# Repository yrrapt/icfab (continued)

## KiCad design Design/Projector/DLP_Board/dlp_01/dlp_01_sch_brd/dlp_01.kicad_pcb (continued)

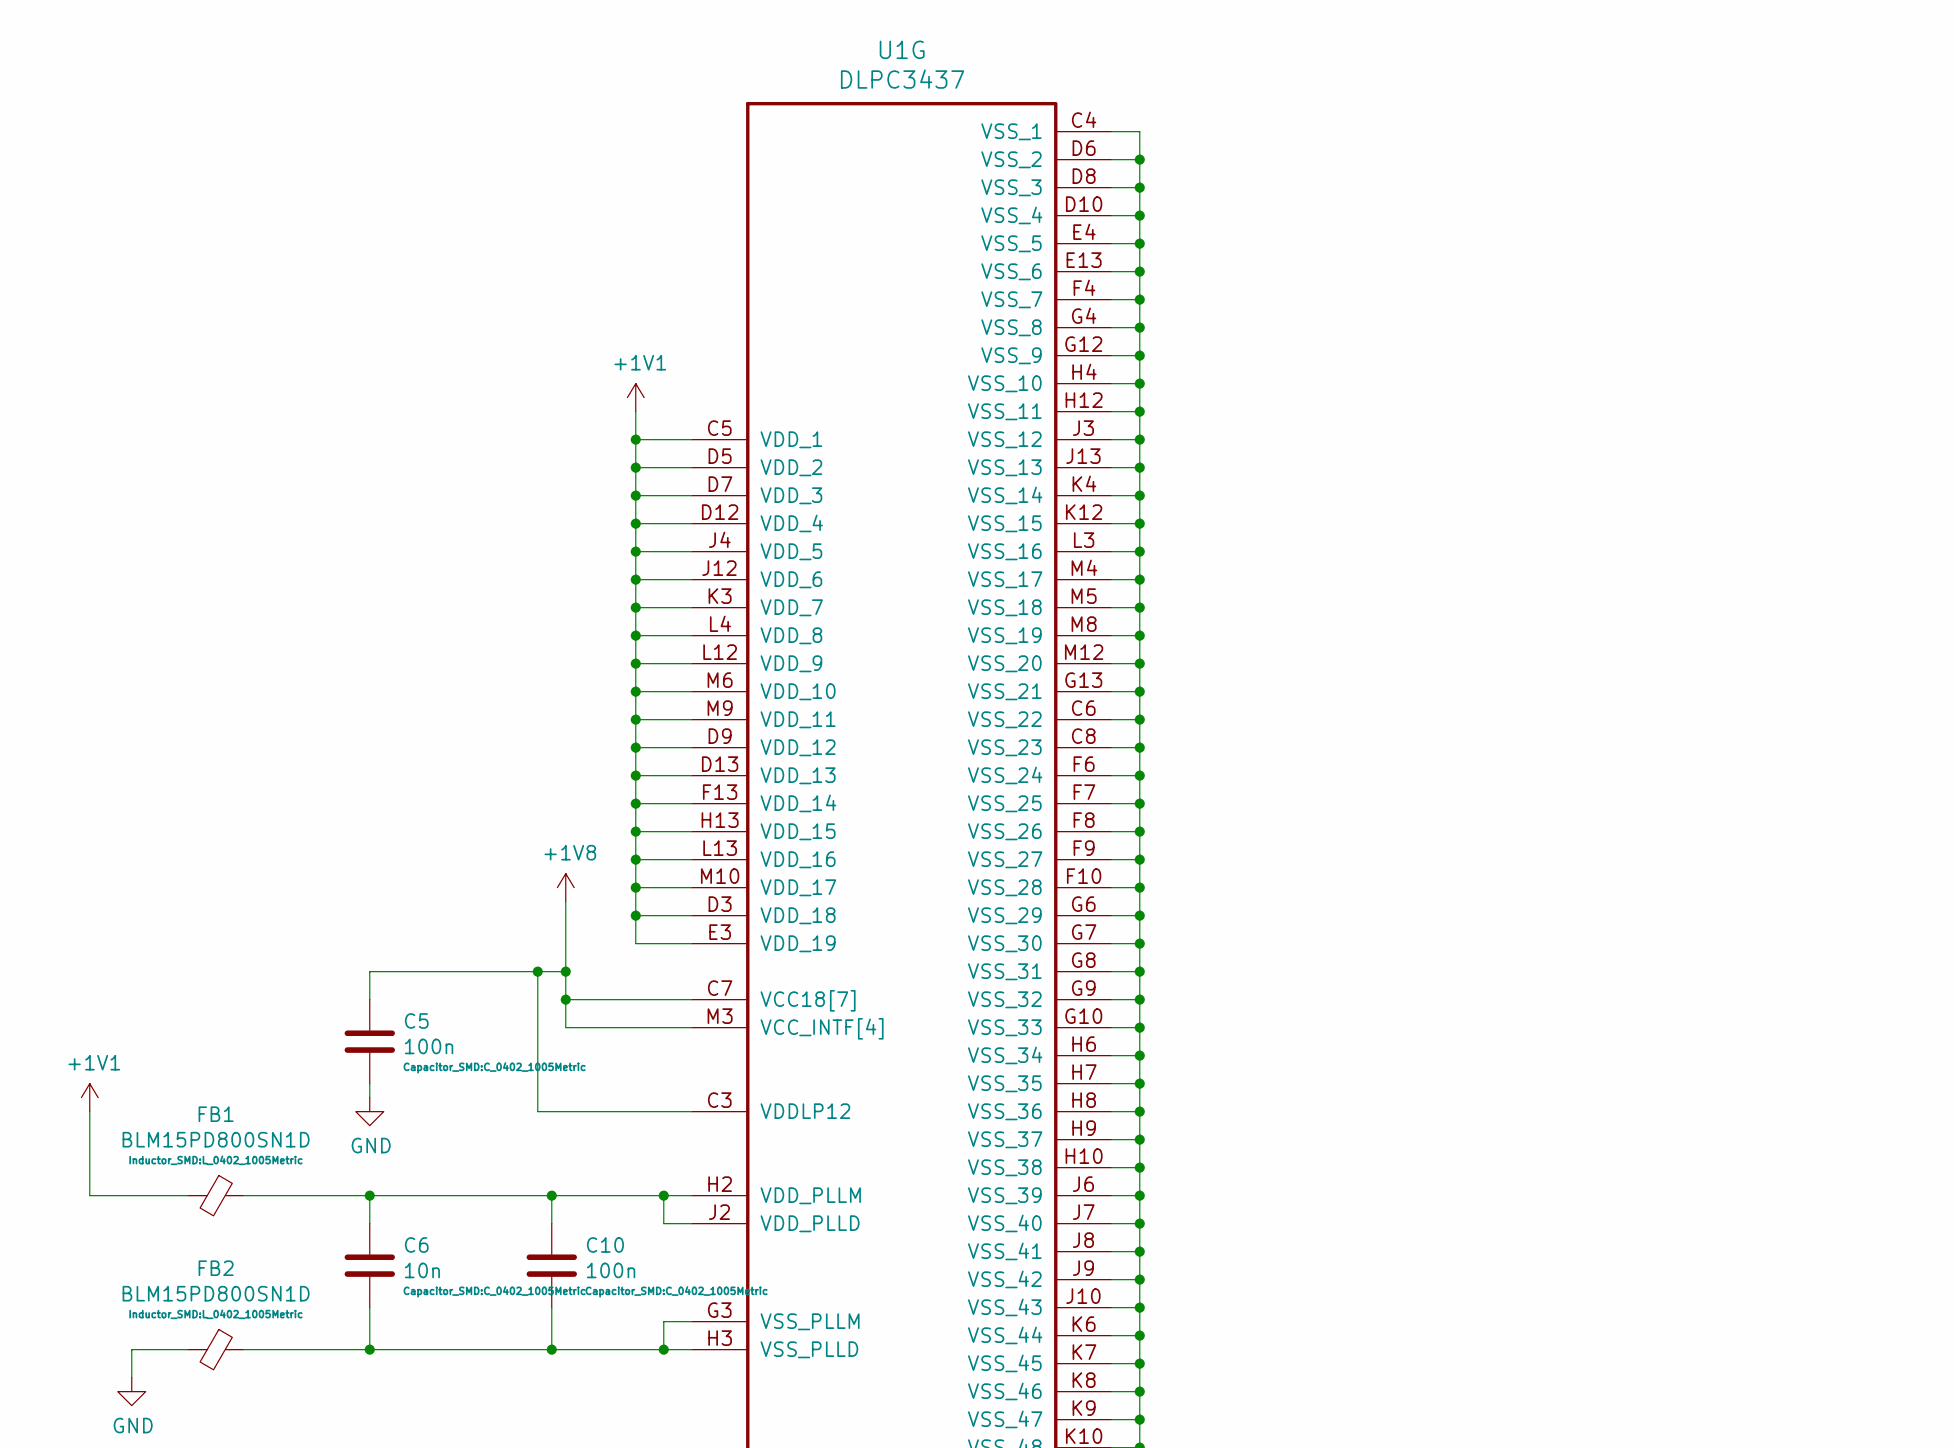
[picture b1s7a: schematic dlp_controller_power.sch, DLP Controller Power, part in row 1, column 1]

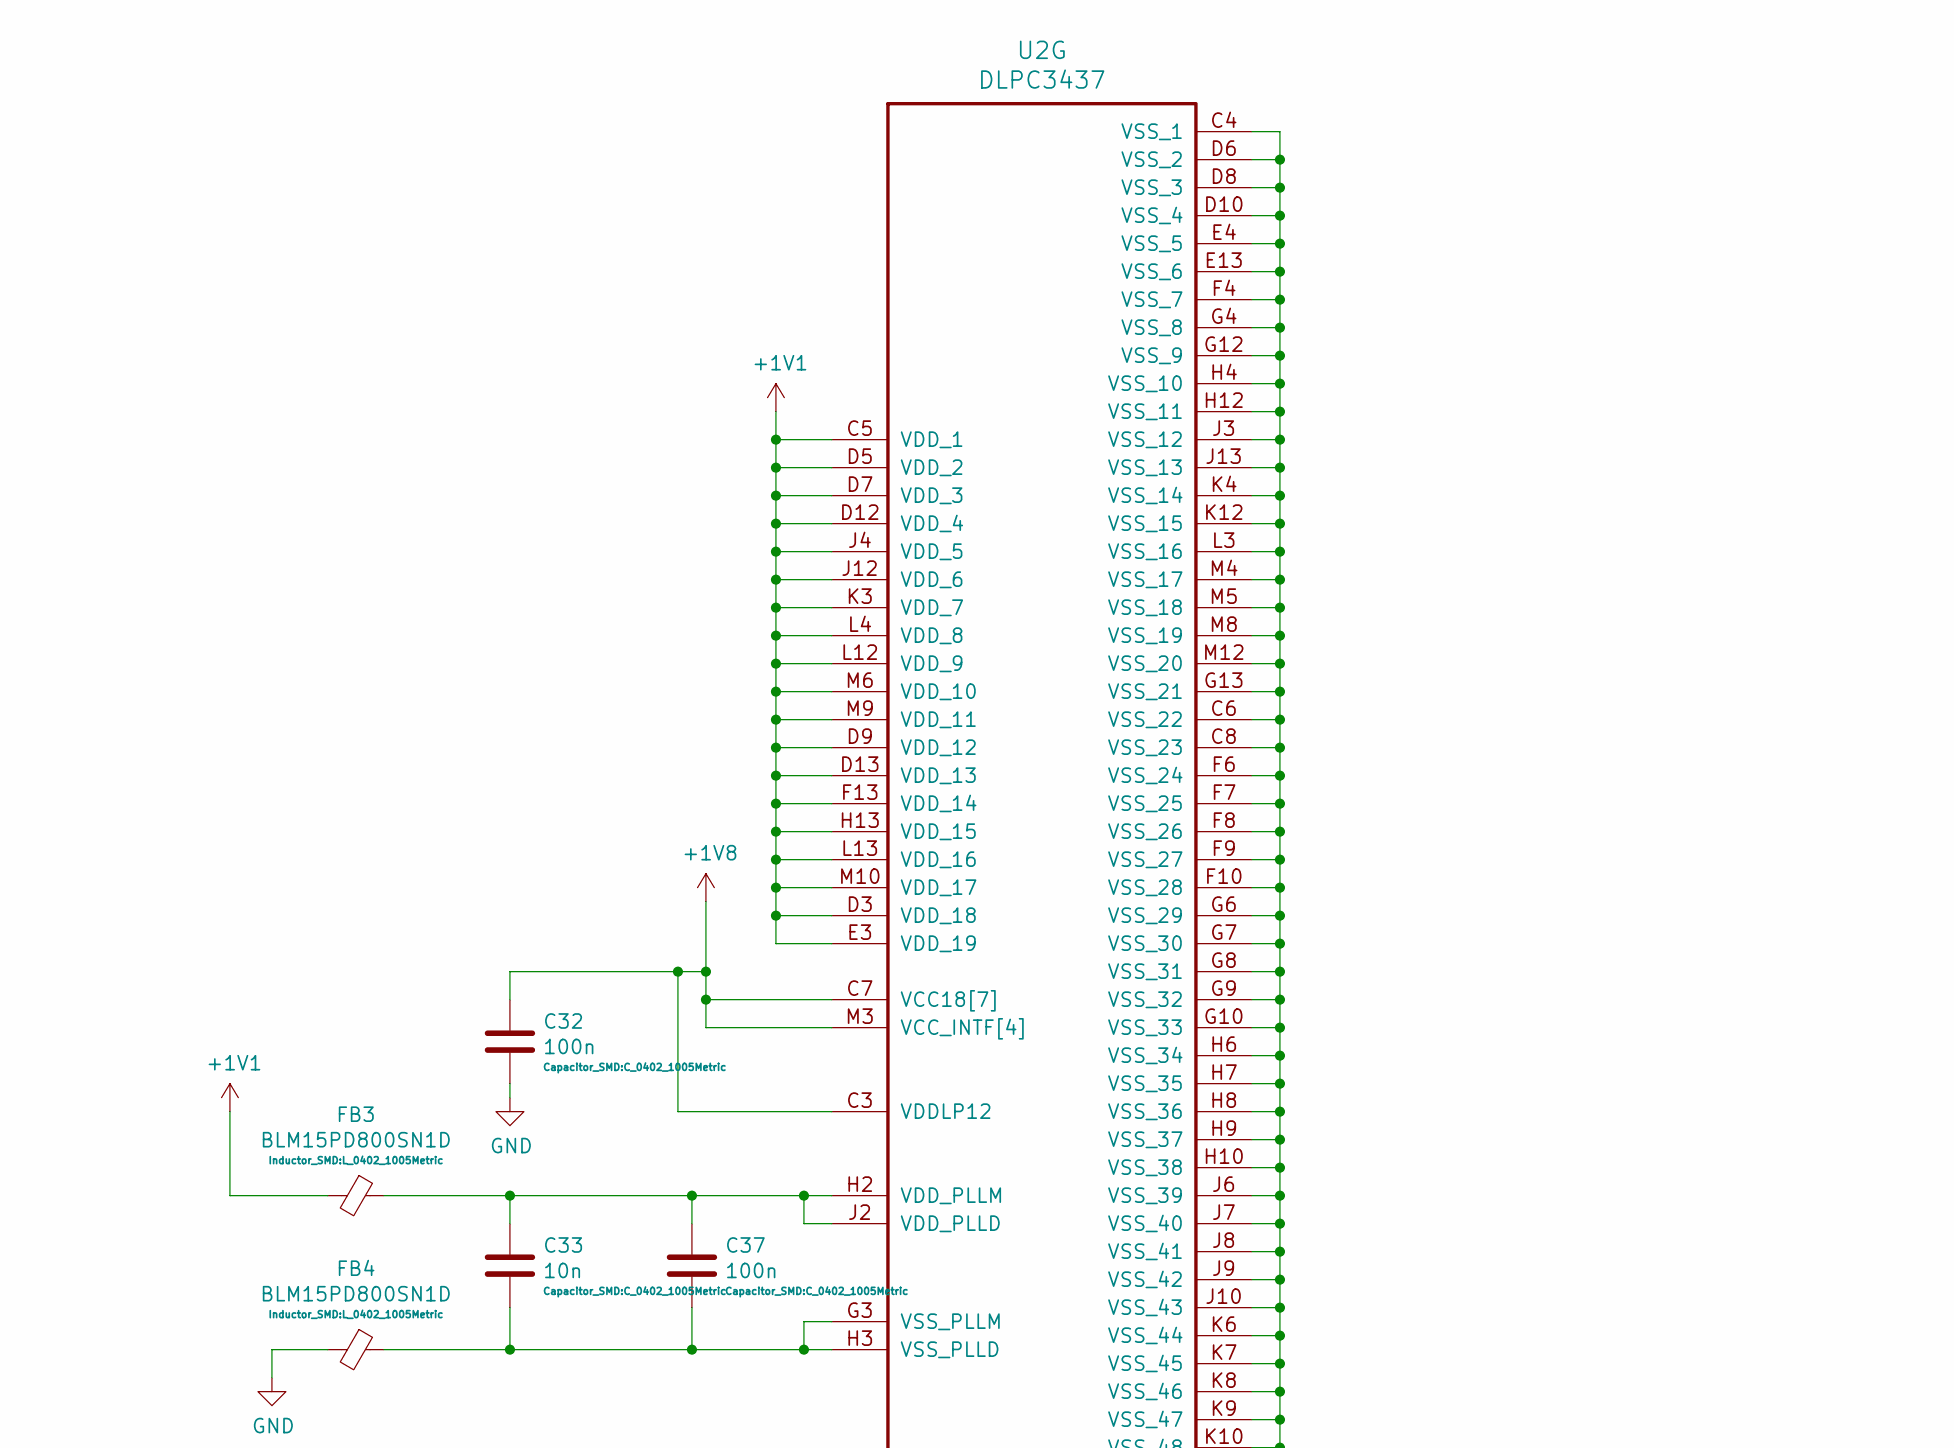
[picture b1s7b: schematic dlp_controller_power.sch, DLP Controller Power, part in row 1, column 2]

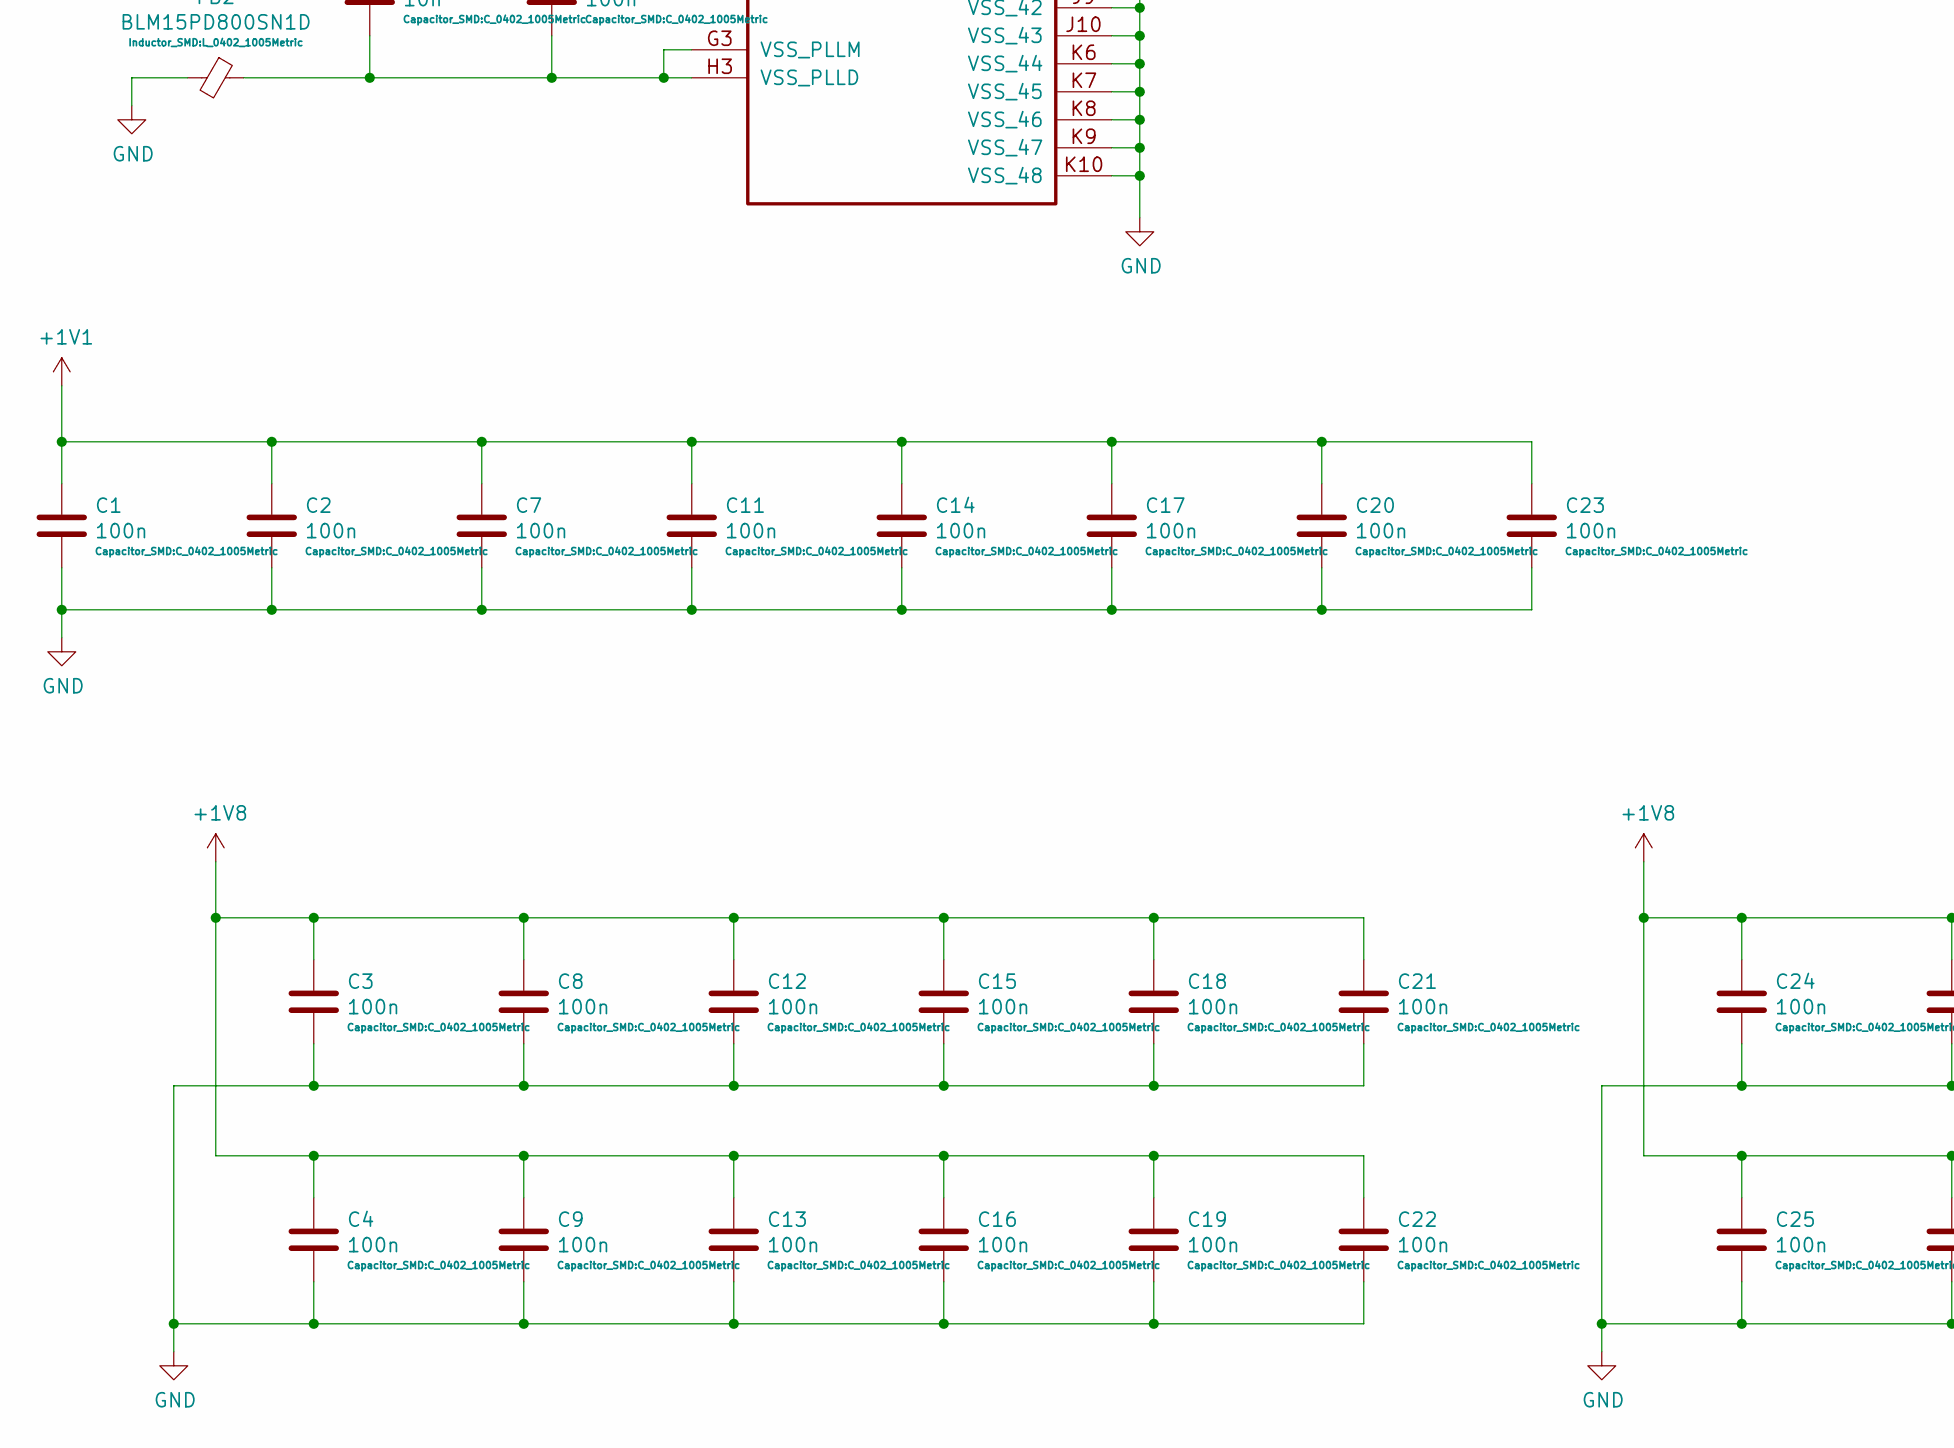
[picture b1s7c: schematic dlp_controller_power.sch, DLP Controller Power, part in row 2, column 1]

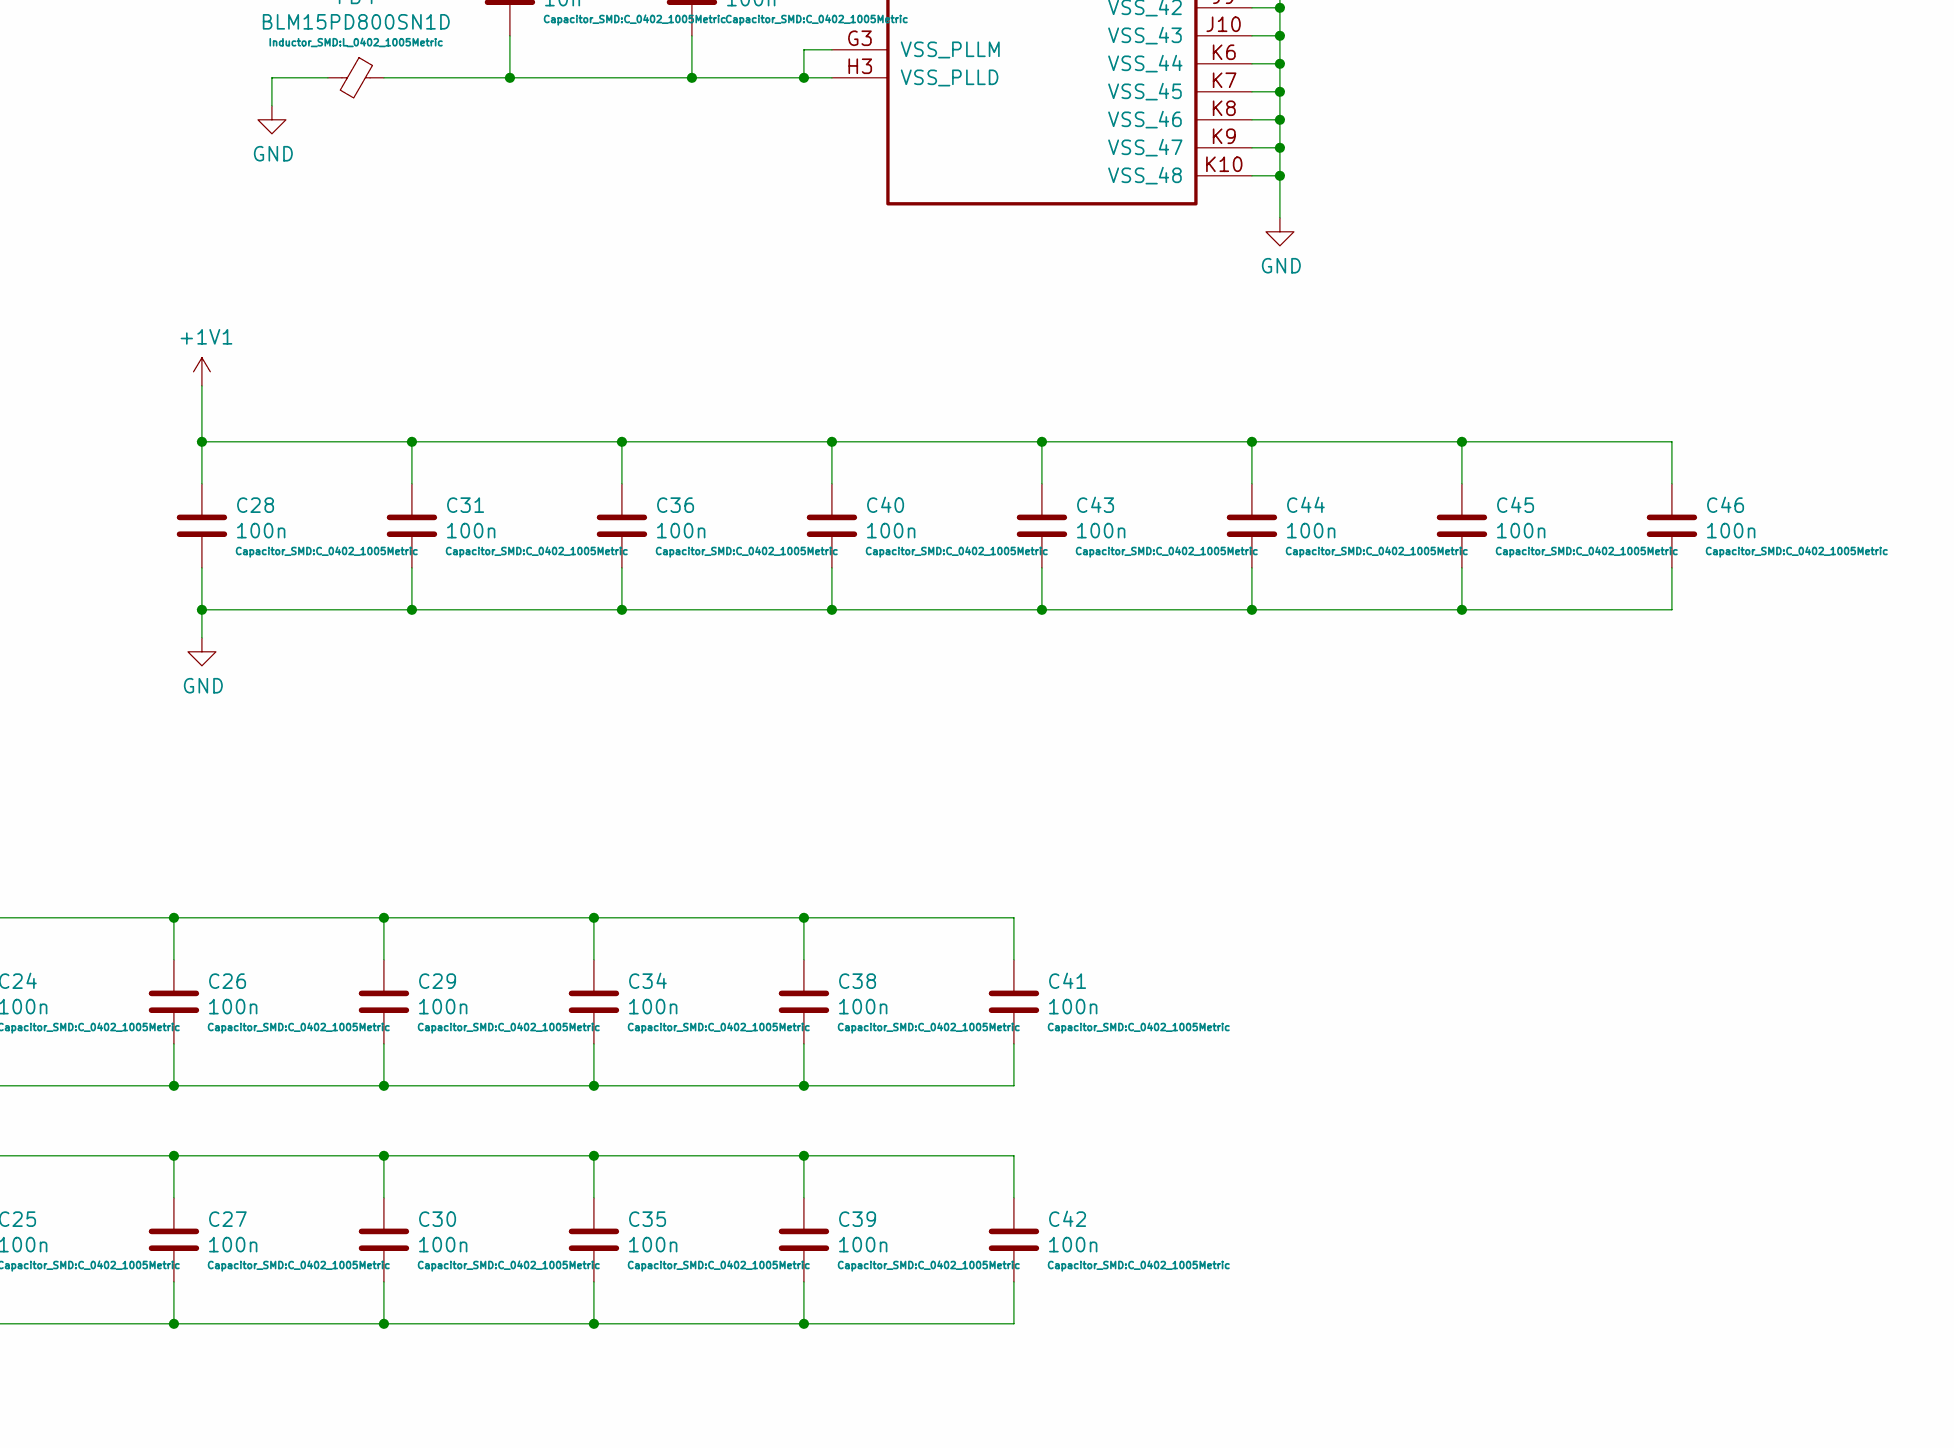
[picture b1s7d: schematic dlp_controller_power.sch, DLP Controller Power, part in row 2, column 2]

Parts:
C1, C2, C3, C4, C5, C7, C8, C9, C10, C11, C12, C13, C14, C15, C16, C17, C18, C19, C20, C21, C22, C23, C24, C25, C26, C27, C28, C29, C30, C31, C32, C34, C35, C36, C37, C38, C39, C40, C41, C42, C43, C44, C45, C46: 100n; C_0402_1005Metric; part-num 0402ZD104KAT2A
C6, C33: 10n; C_0402_1005Metric; part-num 0402ZD103KAT2A
FB1, FB2, FB3, FB4: BLM15PD800SN1D; L_0402_1005Metric; part-num BLM15PD800SN1D
U1, U2: DLPC3437; BGA-225_15x15_13.1x13.1mm; part-num DLPC3437CZEZ

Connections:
+1V1: C1.1, C2.1, C7.1, C11.1, C14.1, C17.1, C20.1, C23.1, C28.1, C31.1, C36.1, C40.1, C43.1, C44.1, C45.1, C46.1, FB1.2, FB3.2, U1.C5 (VDD_1), U1.D3 (VDD_18), U1.D5 (VDD_2), U1.D7 (VDD_3), U1.D9 (VDD_12), U1.D12 (VDD_4), U1.D13 (VDD_13), U1.E3 (VDD_19), U1.F13 (VDD_14), U1.H13 (VDD_15), U1.J4 (VDD_5), U1.J12 (VDD_6), U1.K3 (VDD_7), U1.L4 (VDD_8), U1.L12 (VDD_9), U1.L13 (VDD_16), U1.M6 (VDD_10), U1.M9 (VDD_11), U1.M10 (VDD_17), U2.C5 (VDD_1), U2.D3 (VDD_18), U2.D5 (VDD_2), U2.D7 (VDD_3), U2.D9 (VDD_12), U2.D12 (VDD_4), U2.D13 (VDD_13), U2.E3 (VDD_19), U2.F13 (VDD_14), U2.H13 (VDD_15), U2.J4 (VDD_5), U2.J12 (VDD_6), U2.K3 (VDD_7), U2.L4 (VDD_8), U2.L12 (VDD_9), U2.L13 (VDD_16), U2.M6 (VDD_10), U2.M9 (VDD_11), U2.M10 (VDD_17); also elsewhere on the board
+1V8: C3.1, C4.1, C5.1, C8.1, C9.1, C12.1, C13.1, C15.1, C16.1, C18.1, C19.1, C21.1, C22.1, C24.1, C25.1, C26.1, C27.1, C29.1, C30.1, C32.1, C34.1, C35.1, C38.1, C39.1, C41.1, C42.1, U1.C3 (VDDLP12), U1.C7 (VCC18[7]), U1.C9 (VCC18[7]), U1.D4 (VCC18[7]), U1.E12 (VCC18[7]), U1.F12 (VCC18[7]), U1.K13 (VCC18[7]), U1.M3 (VCC_INTF[4]), U1.M7 (VCC_INTF[4]), U1.M11 (VCC18[7]), U1.N3 (VCC_INTF[4]), U1.N7 (VCC_INTF[4]), U2.C3 (VDDLP12), U2.C7 (VCC18[7]), U2.C9 (VCC18[7]), U2.D4 (VCC18[7]), U2.E12 (VCC18[7]), U2.F12 (VCC18[7]), U2.K13 (VCC18[7]), U2.M3 (VCC_INTF[4]), U2.M7 (VCC_INTF[4]), U2.M11 (VCC18[7]), U2.N3 (VCC_INTF[4]), U2.N7 (VCC_INTF[4]); also elsewhere on the board
GND: C1.2, C2.2, C3.2, C4.2, C5.2, C7.2, C8.2, C9.2, C11.2, C12.2, C13.2, C14.2, C15.2, C16.2, C17.2, C18.2, C19.2, C20.2, C21.2, C22.2, C23.2, C24.2, C25.2, C26.2, C27.2, C28.2, C29.2, C30.2, C31.2, C32.2, C34.2, C35.2, C36.2, C38.2, C39.2, C40.2, C41.2, C42.2, C43.2, C44.2, C45.2, C46.2, FB2.2, FB4.2, U1.C4 (VSS_1), U1.C6 (VSS_22), U1.C8 (VSS_23), U1.D6 (VSS_2), U1.D8 (VSS_3), U1.D10 (VSS_4), U1.E4 (VSS_5), U1.E13 (VSS_6), U1.F4 (VSS_7), U1.F6 (VSS_24), U1.F7 (VSS_25), U1.F8 (VSS_26), U1.F9 (VSS_27), U1.F10 (VSS_28), U1.G4 (VSS_8), U1.G6 (VSS_29), U1.G7 (VSS_30), U1.G8 (VSS_31), U1.G9 (VSS_32), U1.G10 (VSS_33), U1.G12 (VSS_9), U1.G13 (VSS_21), U1.H4 (VSS_10), U1.H6 (VSS_34), U1.H7 (VSS_35), U1.H8 (VSS_36), U1.H9 (VSS_37), U1.H10 (VSS_38), U1.H12 (VSS_11), U1.J3 (VSS_12), U1.J6 (VSS_39), U1.J7 (VSS_40), U1.J8 (VSS_41), U1.J9 (VSS_42), U1.J10 (VSS_43), U1.J13 (VSS_13), U1.K4 (VSS_14), U1.K6 (VSS_44), U1.K7 (VSS_45), U1.K8 (VSS_46), U1.K9 (VSS_47), U1.K10 (VSS_48), U1.K12 (VSS_15), U1.L3 (VSS_16), U1.M4 (VSS_17), U1.M5 (VSS_18), U1.M8 (VSS_19), U1.M12 (VSS_20), U2.C4 (VSS_1), U2.C6 (VSS_22), U2.C8 (VSS_23), U2.D6 (VSS_2), U2.D8 (VSS_3), U2.D10 (VSS_4), U2.E4 (VSS_5), U2.E13 (VSS_6), U2.F4 (VSS_7), U2.F6 (VSS_24), U2.F7 (VSS_25), U2.F8 (VSS_26), U2.F9 (VSS_27), U2.F10 (VSS_28), U2.G4 (VSS_8), U2.G6 (VSS_29), U2.G7 (VSS_30), U2.G8 (VSS_31), U2.G9 (VSS_32), U2.G10 (VSS_33), U2.G12 (VSS_9), U2.G13 (VSS_21), U2.H4 (VSS_10), U2.H6 (VSS_34), U2.H7 (VSS_35), U2.H8 (VSS_36), U2.H9 (VSS_37), U2.H10 (VSS_38), U2.H12 (VSS_11), U2.J3 (VSS_12), U2.J6 (VSS_39), U2.J7 (VSS_40), U2.J8 (VSS_41), U2.J9 (VSS_42), U2.J10 (VSS_43), U2.J13 (VSS_13), U2.K4 (VSS_14), U2.K6 (VSS_44), U2.K7 (VSS_45), U2.K8 (VSS_46), U2.K9 (VSS_47), U2.K10 (VSS_48), U2.K12 (VSS_15), U2.L3 (VSS_16), U2.M4 (VSS_17), U2.M5 (VSS_18), U2.M8 (VSS_19), U2.M12 (VSS_20); also elsewhere on the board
unnamed: C6.1, C10.1, FB1.1, U1.H2 (VDD_PLLM), U1.J2 (VDD_PLLD)
unnamed: C6.2, C10.2, FB2.1, U1.G3 (VSS_PLLM), U1.H3 (VSS_PLLD)
unnamed: C33.1, C37.1, FB3.1, U2.H2 (VDD_PLLM), U2.J2 (VDD_PLLD)
unnamed: C33.2, C37.2, FB4.1, U2.G3 (VSS_PLLM), U2.H3 (VSS_PLLD)

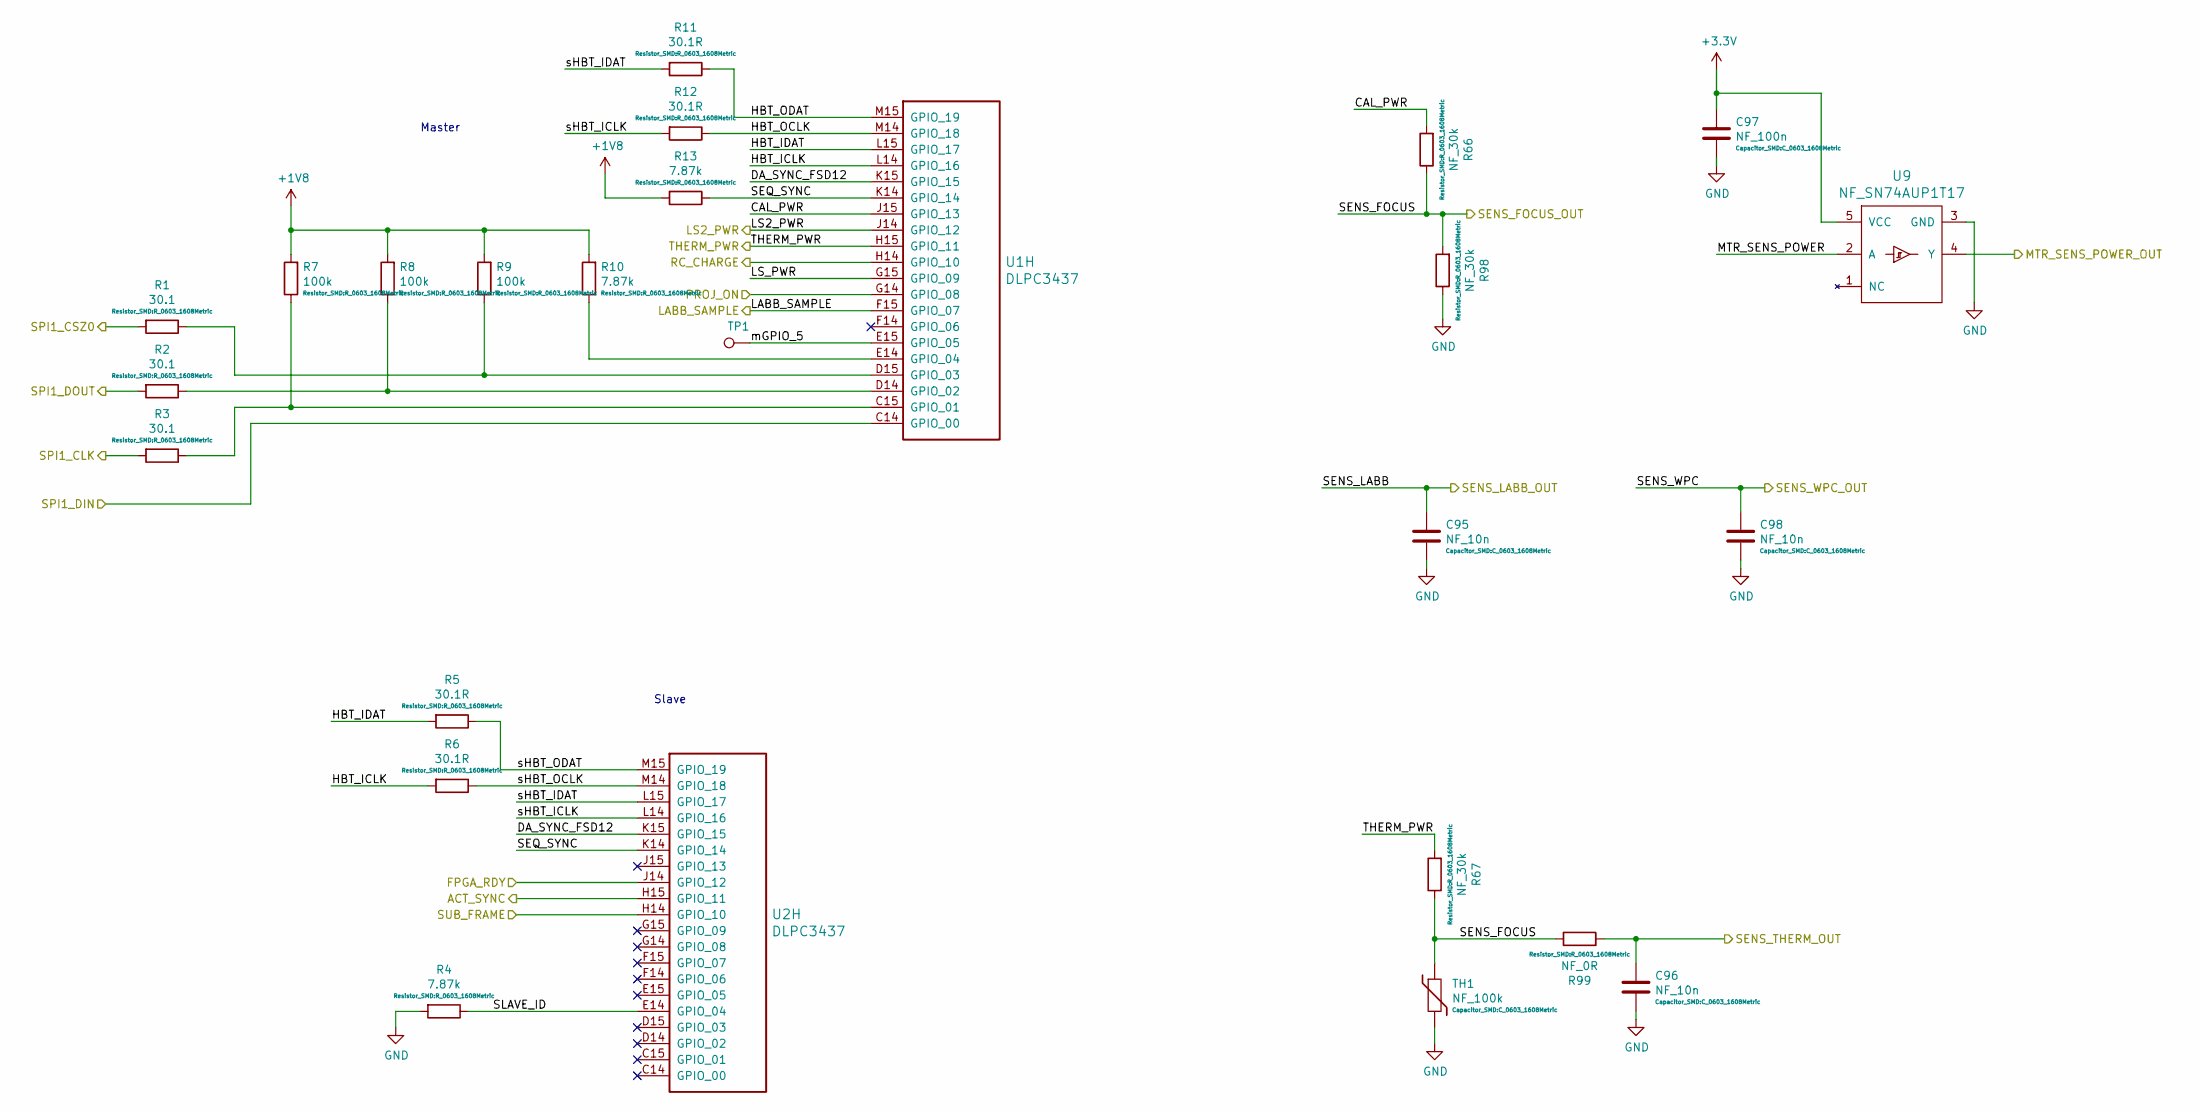
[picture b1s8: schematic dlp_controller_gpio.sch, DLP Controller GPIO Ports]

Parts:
C95, C96, C98: NF_10n; C_0603_1608Metric; part-num NF
C97: NF_100n; C_0603_1608Metric; part-num NF
R1, R2, R3: 30.1; R_0603_1608Metric; part-num CRCW060330R1FKEA
R4, R10, R13: 7.87k; R_0603_1608Metric; part-num CRCW06037K87FKEA
R5, R6, R11, R12: 30.1R; R_0603_1608Metric; part-num CRCW060330R1FKEA
R7, R8, R9: 100k; R_0603_1608Metric; part-num CRCW0603100KFKEA
R66, R67, R98: NF_30k; R_0603_1608Metric; part-num NF
R99: NF_0R; R_0603_1608Metric; part-num NF
TH1: NF_100k; C_0603_1608Metric; part-num NF
TP1: TestPoint; TestPoint_Pad_D1.5mm
U1, U2: DLPC3437; BGA-225_15x15_13.1x13.1mm; part-num DLPC3437CZEZ
U9: NF_SN74AUP1T17; SC-70-5; part-num SN74AUP1T17

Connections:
+1V8: R7.2, R8.2, R9.2, R10.2, R13.2; also elsewhere on the board
/LS2_PWR: U1.J14 (GPIO_12); also elsewhere on the board
/MTR_SENS_POWER_OUT: U9.4 (Y); also elsewhere on the board
/SENS_FOCUS_OUT: R66.1, R67.1, R98.2, R99.1, TH1.1
/SENS_LABB_OUT: C95.1
/SENS_THERM_OUT: C96.1, R99.2
/SENS_WPC_OUT: C98.1
/THERM_PWR: R67.2, U1.H15 (GPIO_11); also elsewhere on the board
/application_connectors/ACT_SYNC: U2.H15 (GPIO_11); also elsewhere on the board
/application_connectors/FPGA_RDY: U2.J14 (GPIO_12); also elsewhere on the board
/application_connectors/PROJ_ON: U1.G14 (GPIO_08); also elsewhere on the board
/application_connectors/SUB_FRAME: U2.H14 (GPIO_10); also elsewhere on the board
/dlp_controller/LABB_SAMPLE: U1.F15 (GPIO_07); also elsewhere on the board
/dlp_controller/RC_CHARGE: U1.H14 (GPIO_10); also elsewhere on the board
/dlp_controller/dlp_controller_gpio/CAL_PWR: R66.2, U1.J15 (GPIO_13)
/dlp_controller/dlp_controller_gpio/DA_SYNC_FSD12: U1.K15 (GPIO_15), U2.K15 (GPIO_15)
/dlp_controller/dlp_controller_gpio/HBT_ICLK: R6.2, U1.L14 (GPIO_16)
/dlp_controller/dlp_controller_gpio/HBT_IDAT: R5.2, U1.L15 (GPIO_17)
/dlp_controller/dlp_controller_gpio/HBT_OCLK: R12.1, U1.M14 (GPIO_18)
/dlp_controller/dlp_controller_gpio/HBT_ODAT: R11.1, U1.M15 (GPIO_19)
/dlp_controller/dlp_controller_gpio/LS_PWR: U1.G15 (GPIO_09)
/dlp_controller/dlp_controller_gpio/MTR_SENS_POWER: U9.2 (A)
/dlp_controller/dlp_controller_gpio/SEQ_SYNC: R13.1, U1.K14 (GPIO_14), U2.K14 (GPIO_14)
/dlp_controller/dlp_controller_gpio/SLAVE_ID: R4.1, U2.E14 (GPIO_04)
/dlp_controller/dlp_controller_gpio/SPI1_CLK: R3.2; also elsewhere on the board
/dlp_controller/dlp_controller_gpio/SPI1_CSZ0: R1.2; also elsewhere on the board
/dlp_controller/dlp_controller_gpio/SPI1_DIN: U1.C14 (GPIO_00); also elsewhere on the board
/dlp_controller/dlp_controller_gpio/SPI1_DOUT: R2.2; also elsewhere on the board
/dlp_controller/dlp_controller_gpio/mGPIO_5: TP1.1, U1.E15 (GPIO_05)
/dlp_controller/dlp_controller_gpio/sHBT_ICLK: R12.2, U2.L14 (GPIO_16)
/dlp_controller/dlp_controller_gpio/sHBT_IDAT: R11.2, U2.L15 (GPIO_17)
/dlp_controller/dlp_controller_gpio/sHBT_OCLK: R6.1, U2.M14 (GPIO_18)
/dlp_controller/dlp_controller_gpio/sHBT_ODAT: R5.1, U2.M15 (GPIO_19)
GND: C95.2, C96.2, C97.2, C98.2, R4.2, R98.1, TH1.2, U9.3 (GND); also elsewhere on the board
unnamed: R1.1, R9.1, U1.D15 (GPIO_03)
unnamed: R2.1, R8.1, U1.D14 (GPIO_02)
unnamed: R3.1, R7.1, U1.C15 (GPIO_01)
unnamed: R10.1, U1.E14 (GPIO_04)

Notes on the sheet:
Master
Slave

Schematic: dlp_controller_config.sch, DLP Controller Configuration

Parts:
C47, C99, C100: 100n; C_0603_1608Metric; part-num 06033C104KAT4A
R14, R15, R22, R26, R30, R33, R34, R40: 100k; R_0603_1608Metric; part-num CRCW0603100KFKEA
R16, R20, R23, R25, R27, R38, R41, R43, R44: 30.1R; R_0603_1608Metric; part-num CRCW060330R1FKEA
R17, R18, R28, R29, R35, R36, R46, R47: 0R; R_0603_1608Metric; part-num CRCW06030000Z0EAC
R19, R37, R45: 10k; R_0603_1608Metric; part-num CRCW060310K0FKEA
R21, R24, R39, R42: 2k; R_0603_1608Metric; part-num CRCW06032K00FKEA
R31, R32: 8.2k; R_0603_1608Metric; part-num CRCW06038K20FKEA
TP2, TP3, TP4, TP5, TP6, TP7, TP8, TP9, TP10, TP11: TestPoint; TestPoint_Pad_D1.5mm
U1, U2: DLPC3437; BGA-225_15x15_13.1x13.1mm; part-num DLPC3437CZEZ
U3: ASDMB-24.000MHZ-LC-T; Oscillator_SMD_SeikoEpson_SG210-4Pin_2.5x2.0mm_HandSoldering; part-num ASDMB-24.000MHZ-LC-T
U4, U5: W25Q64JVSSIQ; SO-8_5.3x6.2mm_P1.27mm; part-num W25Q64JVSSIQ

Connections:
+1V8: C47.1, R19.1, R21.1, R24.1, R37.1, R39.1, R42.1, U3.4 (VDD); also elsewhere on the board
/application_connectors/CONTR0_SCL: R17.2, R46.2; also elsewhere on the board
/application_connectors/CONTR0_SDA: R18.1, R47.1; also elsewhere on the board
/application_connectors/CONTR1_SCL: R35.2; also elsewhere on the board
/application_connectors/CONTR1_SDA: R36.1; also elsewhere on the board
/application_connectors/HOST_SCL: R28.2; also elsewhere on the board
/application_connectors/HOST_SDA: R29.1; also elsewhere on the board
/application_connectors/mHOST_IRQ: R19.2, U1.N8 (HOST_IRQ); also elsewhere on the board
/application_connectors/sHOST_IRQ: R37.2, U2.N8 (HOST_IRQ); also elsewhere on the board
/dlp_controller/CMP_OUT: U1.A12 (CMP_OUT); also elsewhere on the board
/dlp_controller/LED_SEL_0: R26.1, U1.B14 (LED_SEL_1); also elsewhere on the board
/dlp_controller/LED_SEL_1: R30.1, U1.B15 (LED_SEL_0); also elsewhere on the board
/dlp_controller/RESETZ: U1.C11 (RESERVED_8), U2.C11 (RESERVED_8); also elsewhere on the board
/dlp_controller/dlp_controller_config/mSPI_CLK: R15.1, R27.2, U4.6 (CLK); also elsewhere on the board
/dlp_controller/dlp_controller_config/mSPI_CSZO: R14.2, R23.2, U4.1 (~CS); also elsewhere on the board
/dlp_controller/dlp_controller_config/mSPI_MISO: R20.1, R22.1, U1.B12 (SPI0_DIN); also elsewhere on the board
/dlp_controller/dlp_controller_config/mSPI_MOSI: R25.2, U4.5 (DI(IO0)); also elsewhere on the board
/dlp_controller/dlp_controller_config/sSPI_CLK: R34.1, R44.2, U5.6 (CLK); also elsewhere on the board
/dlp_controller/dlp_controller_config/sSPI_CSZO: R33.2, R41.2, U5.1 (~CS); also elsewhere on the board
/dlp_controller/dlp_controller_config/sSPI_MISO: R38.1, R40.1, U2.B12 (SPI0_DIN); also elsewhere on the board
/dlp_controller/dlp_controller_config/sSPI_MOSI: R43.2, U5.5 (DI(IO0)); also elsewhere on the board
/dlp_pmic/INTZ: U1.C13 (PARKZ), U2.C13 (PARKZ); also elsewhere on the board
GND: C47.2, C99.2, C100.2, R15.2, R22.2, R26.2, R30.2, R31.1, R32.1, R34.2, R40.2, R45.2, U1.C10 (HWTEST_EN), U2.C10 (HWTEST_EN), U3.2 (GND), U4.4 (GND), U5.4 (GND); also elsewhere on the board
unnamed: R16.1, U1.H1 (PLL_REFCLK_I), U2.H1 (PLL_REFCLK_I)
unnamed: R16.2, U3.3 (Out)
unnamed: R17.1, R24.2, U1.R11 (IIC1_SCL)
unnamed: R18.2, R21.2, U1.R10 (IIC1_SDA)
unnamed: R20.2, U4.2 (DO(IO1))
unnamed: R23.1, U1.A14 (SPI0_CSZ0)
unnamed: R25.1, U1.B13 (SPI0_DOUT)
unnamed: R27.1, U1.A13 (SPI0_CLK)
unnamed: R28.1, U1.N10 (IIC0_SCL)
unnamed: R29.2, U1.N9 (IIC0_SDA)
unnamed: R31.2, U1.P11 (RESERVED_7)
unnamed: R32.2, U2.P11 (RESERVED_7)
unnamed: R35.1, R42.2, U2.R11 (IIC1_SCL)
unnamed: R36.2, R39.2, U2.R10 (IIC1_SDA)
unnamed: R38.2, U5.2 (DO(IO1))
unnamed: R41.1, U2.A14 (SPI0_CSZ0)
unnamed: R43.1, U2.B13 (SPI0_DOUT)
unnamed: R44.1, U2.A13 (SPI0_CLK)
unnamed: R45.1, U2.A12 (CMP_OUT)
unnamed: R46.1, U2.N10 (IIC0_SCL)
unnamed: R47.2, U2.N9 (IIC0_SDA)
unnamed: TP2.1, U1.R12 (TSTPT_0)
unnamed: TP3.1, U1.R13 (TSTPT_1)
unnamed: TP4.1, U1.R14 (TSTPT_2)
unnamed: TP5.1, U1.R15 (TSTPT_3)
unnamed: TP6.1, U1.P14 (TSTPT_4)
unnamed: TP7.1, U1.P15 (TSTPT_5)
unnamed: TP8.1, U1.N14 (TSTPT_6)
unnamed: TP9.1, U1.N15 (TSTPT_7)
unnamed: TP10.1, U1.A15 (CMP_PWM)
unnamed: TP11.1, U3.1 (Standby)

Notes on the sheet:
Master
Slave
